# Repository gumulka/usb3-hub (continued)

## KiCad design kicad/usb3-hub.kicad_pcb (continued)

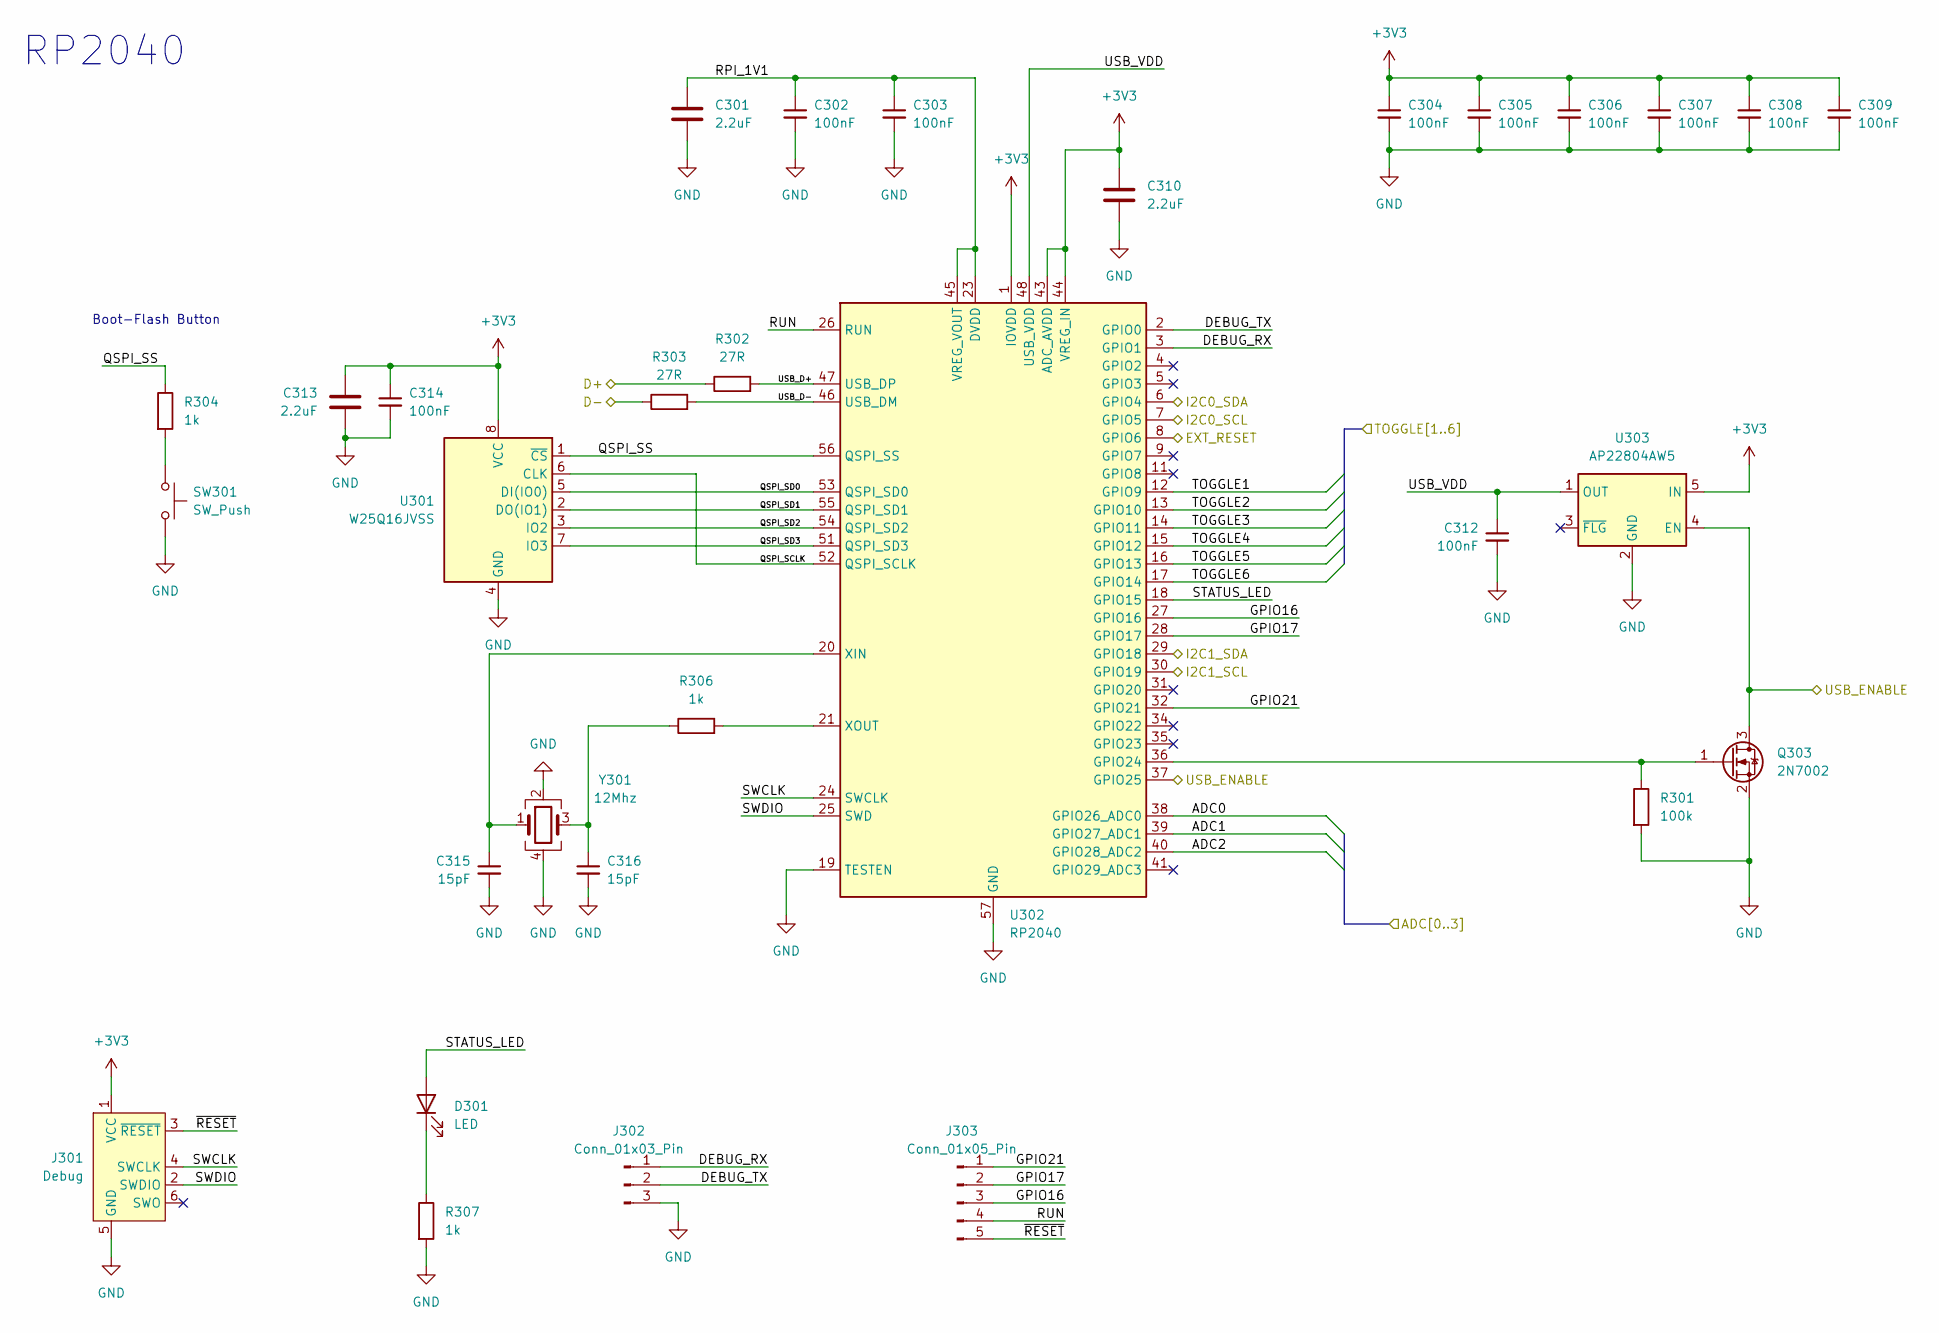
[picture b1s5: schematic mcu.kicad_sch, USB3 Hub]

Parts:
C301, C310, C313: 2.2uF; C_0603_1608Metric
C302, C303, C304, C305, C306, C307, C308, C309, C312, C314: 100nF; C_0402_1005Metric
C315, C316: 15pF; C_0402_1005Metric
D301: LED; LED_0603_1608Metric
J301: Debug; Tag-Connect_TC2030-IDC-NL_2x03_P1.27mm_Vertical
J302: Conn_01x03_Pin; PinHeader_1x03_P2.54mm_Vertical
J303: Conn_01x05_Pin; PinSocket_1x05_P2.54mm_Vertical
Q303: 2N7002; SOT-23
R301: 100k; R_0603_1608Metric
R302, R303: 27R; R_0402_1005Metric
R304, R306, R307: 1k; R_0603_1608Metric
SW301: SW_Push; SW_SPST_TL3342
U301: W25Q16JVSS; SOIC-8_5.23x5.23mm_P1.27mm
U302: RP2040; QFN-56-1EP_7x7mm_P0.4mm_EP3.2x3.2mm
U303: AP22804AW5; SOT-23-5
Y301: 12Mhz; Crystal_SMD_3225-4Pin_3.2x2.5mm; PartNo ABM8-272-T3

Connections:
+3V3: C304.1, C305.1, C306.1, C307.1, C308.1, C309.1, C310.1, C313.1, C314.1, J301.1 (VCC), U301.8 (VCC), U302.1 (IOVDD), U302.10 (IOVDD), U302.22 (IOVDD), U302.33 (IOVDD), U302.42 (IOVDD), U302.43 (ADC_AVDD), U302.44 (VREG_IN), U302.49 (IOVDD), U303.5 (IN); also elsewhere on the board
/ADC0: U302.38 (GPIO26_ADC0); also elsewhere on the board
/ADC1: U302.39 (GPIO27_ADC1); also elsewhere on the board
/ADC2: U302.40 (GPIO28_ADC2); also elsewhere on the board
/Hub/Port7.DP+: R302.1; also elsewhere on the board
/Hub/Port7.DP-: R303.1; also elsewhere on the board
/Hub/Port7.PRT_CTRL: Q303.3 (D), U302.37 (GPIO25), U303.4 (EN); also elsewhere on the board
/Hub/SMB_CLK: U302.7 (GPIO5); also elsewhere on the board
/Hub/SMB_DATA: U302.6 (GPIO4); also elsewhere on the board
/Hub/~RESET: U302.8 (GPIO6); also elsewhere on the board
/Raspberry/DEBUG_RX: J302.1, U302.3 (GPIO1)
/Raspberry/DEBUG_TX: J302.2, U302.2 (GPIO0)
/Raspberry/GPIO16: J303.3, U302.27 (GPIO16)
/Raspberry/GPIO17: J303.2, U302.28 (GPIO17)
/Raspberry/GPIO21: J303.1, U302.32 (GPIO21)
/Raspberry/I2C1_SCL: U302.30 (GPIO19); also elsewhere on the board
/Raspberry/I2C1_SDA: U302.29 (GPIO18); also elsewhere on the board
/Raspberry/QSPI_SCLK: U301.6 (CLK), U302.52 (QSPI_SCLK)
/Raspberry/QSPI_SD0: U301.5 (DI(IO0)), U302.53 (QSPI_SD0)
/Raspberry/QSPI_SD1: U301.2 (DO(IO1)), U302.55 (QSPI_SD1)
/Raspberry/QSPI_SD2: U301.3 (IO2), U302.54 (QSPI_SD2)
/Raspberry/QSPI_SD3: U301.7 (IO3), U302.51 (QSPI_SD3)
/Raspberry/QSPI_SS: R304.1, U301.1 (~CS), U302.56 (QSPI_SS)
/Raspberry/RPI_1V1: C301.1, C302.1, C303.1, U302.23 (DVDD), U302.45 (VREG_VOUT), U302.50 (DVDD)
/Raspberry/RUN: J303.4, U302.26 (RUN)
/Raspberry/STATUS_LED: D301.2 (A), U302.18 (GPIO15)
/Raspberry/SWCLK: J301.4 (SWCLK), U302.24 (SWCLK)
/Raspberry/SWDIO: J301.2 (SWDIO), U302.25 (SWD)
/Raspberry/USB_D+: R302.2, U302.47 (USB_DP)
/Raspberry/USB_D-: R303.2, U302.46 (USB_DM)
/Raspberry/USB_VDD: C312.1, U302.48 (USB_VDD), U303.1 (OUT)
/Raspberry/~RESET: J301.3 (~RESET), J303.5
/TOGGLE1: U302.12 (GPIO9); also elsewhere on the board
/TOGGLE2: U302.13 (GPIO10); also elsewhere on the board
/TOGGLE3: U302.14 (GPIO11); also elsewhere on the board
/TOGGLE4: U302.15 (GPIO12); also elsewhere on the board
/TOGGLE5: U302.16 (GPIO13); also elsewhere on the board
/TOGGLE6: U302.17 (GPIO14); also elsewhere on the board
GND: C301.2, C302.2, C303.2, C304.2, C305.2, C306.2, C307.2, C308.2, C309.2, C310.2, C312.2, C313.2, C314.2, C315.2, C316.2, J301.5 (GND), J302.3, Q303.2 (S), R301.2, R307.2, SW301.2, U301.4 (GND), U302.19 (TESTEN), U302.57 (GND), U303.2 (GND), Y301.2, Y301.4; also elsewhere on the board
unnamed: C316.1, R306.1, Y301.3
unnamed: D301.1 (K), R307.1
unnamed: Q303.1 (G), R301.1, U302.36 (GPIO24)
unnamed: R304.2, SW301.1
unnamed: C315.1, U302.20 (XIN), Y301.1
unnamed: R306.2, U302.21 (XOUT)

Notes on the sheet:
RP2040
Boot-Flash Button

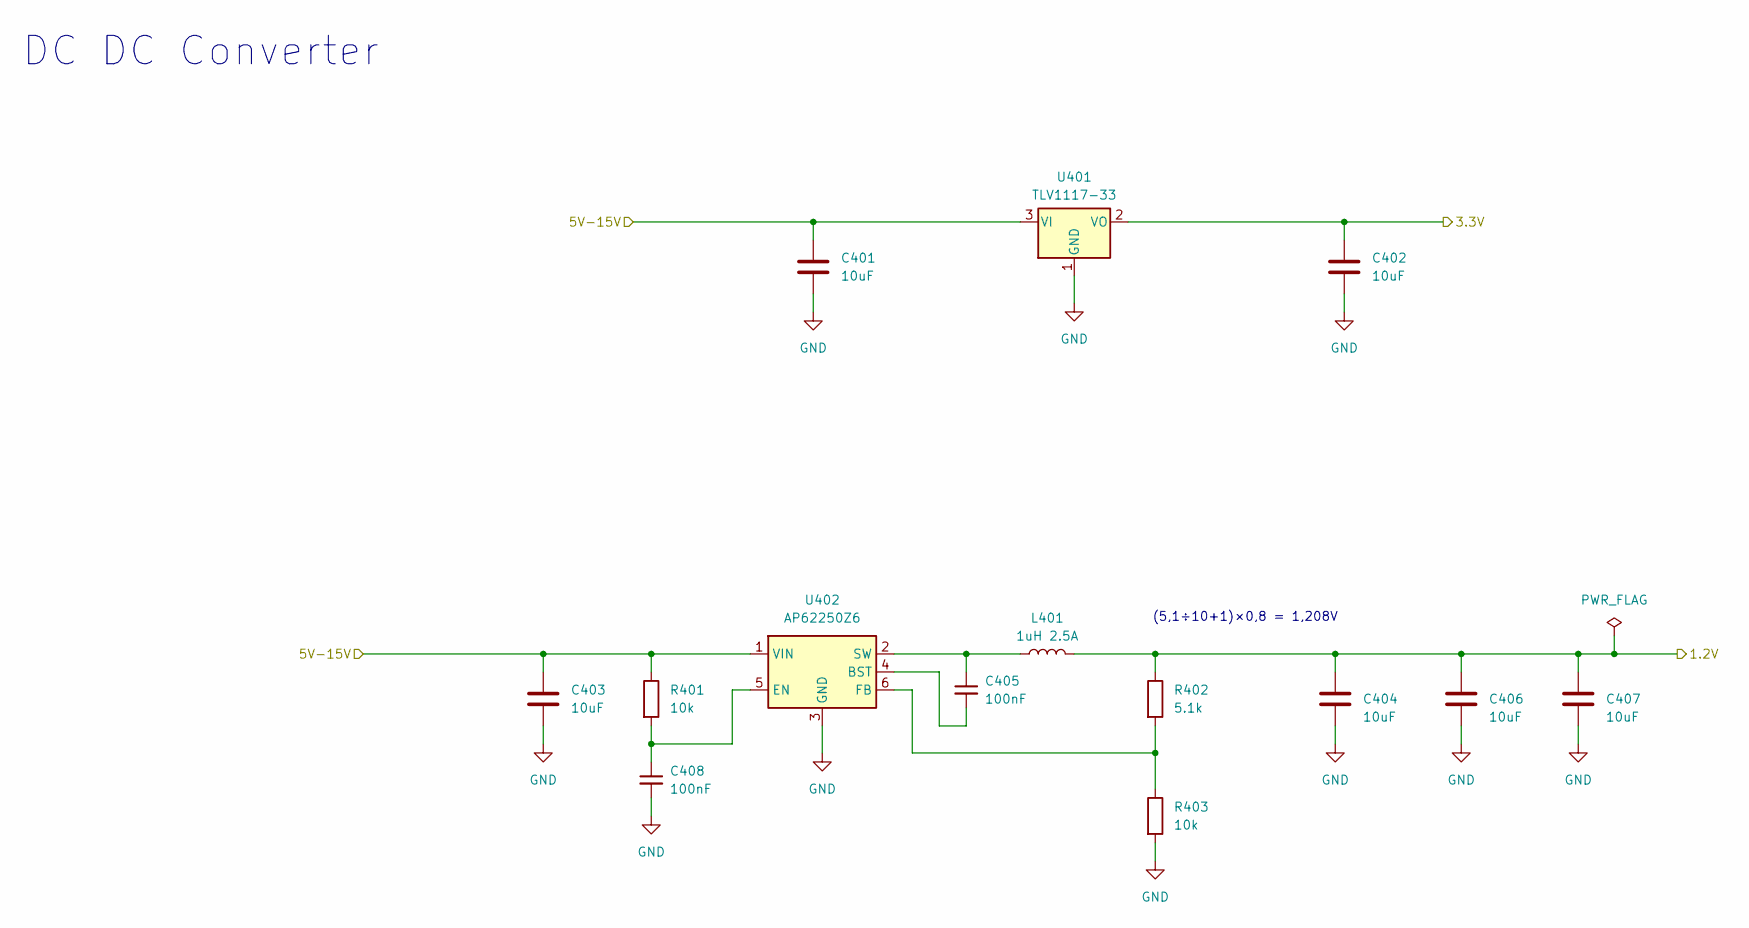
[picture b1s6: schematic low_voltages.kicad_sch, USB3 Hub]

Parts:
C401, C402, C403, C404, C406, C407: 10uF; C_0805_2012Metric
C405, C408: 100nF; C_0402_1005Metric
L401: 1uH 2.5A; L_Bourns-SRN4018
R401, R403: 10k; R_0603_1608Metric
R402: 5.1k; R_0603_1608Metric
U401: TLV1117-33; SOT-223-3_TabPin2
U402: AP62250Z6; SOT-563

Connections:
+1V2: C404.1, C406.1, C407.1, L401.2, R402.1; also elsewhere on the board
+3V3: C402.1, U401.2 (VO); also elsewhere on the board
+5V: C401.1, C403.1, R401.1, U401.3 (VI), U402.1 (VIN); also elsewhere on the board
GND: C401.2, C402.2, C403.2, C404.2, C406.2, C407.2, C408.2, R403.2, U401.1 (GND), U402.3 (GND); also elsewhere on the board
unnamed: C405.2, U402.4 (BST)
unnamed: C408.1, R401.2, U402.5 (EN)
unnamed: R402.2, R403.1, U402.6 (FB)
unnamed: C405.1, L401.1, U402.2 (SW)

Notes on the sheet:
DC DC Converter
(5,1÷10+1)×0,8 = 1,208V

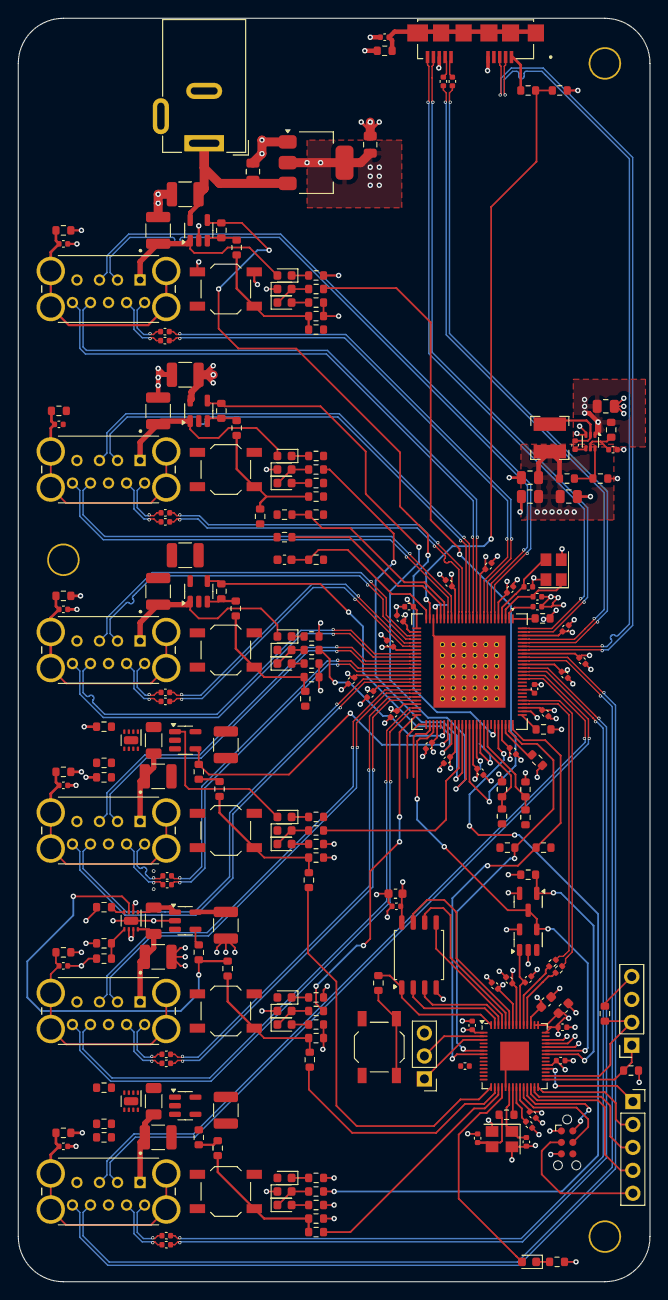
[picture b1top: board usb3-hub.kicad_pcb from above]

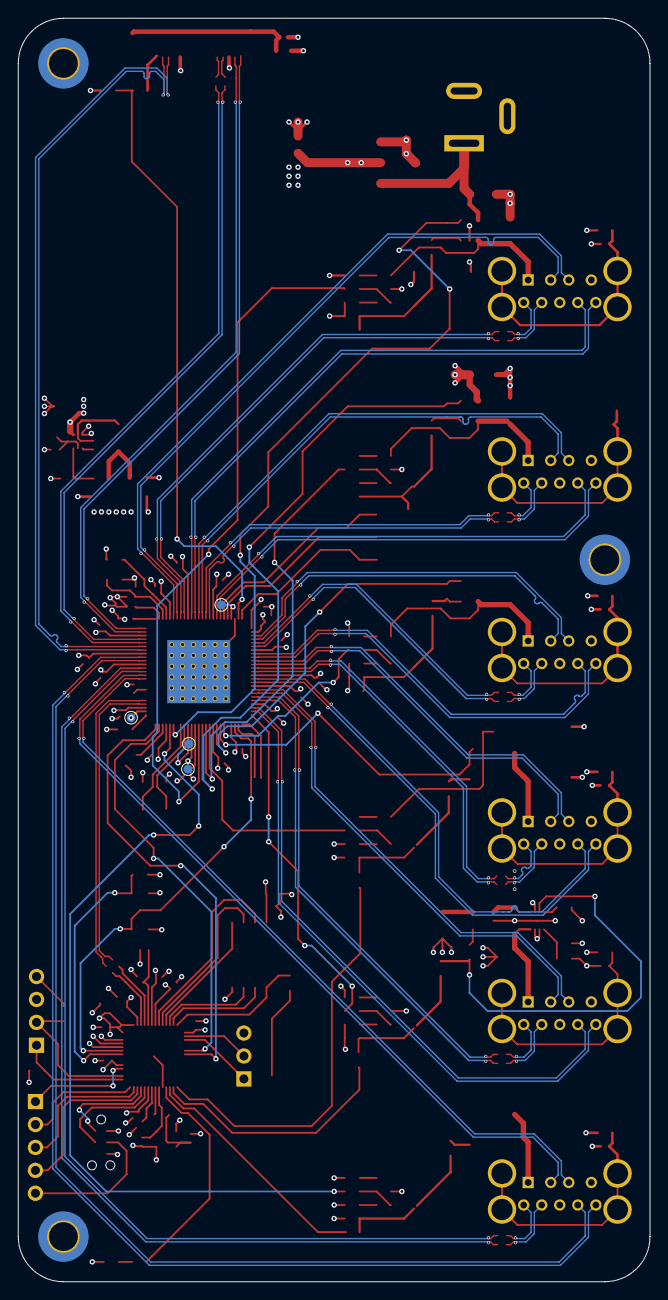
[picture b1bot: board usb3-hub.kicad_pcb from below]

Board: 6 copper layers, 70.0 x 140.0 mm, 229 parts (7 on the bottom side), 186 nets.

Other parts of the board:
D501, D502, D503, D601, D602, D603: LED; LED_0603_1608Metric

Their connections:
/Port4/VBUS_HIGH: D501.2 (A); also elsewhere on the board
/Port5/VBUS_HIGH: D601.2 (A); also elsewhere on the board
GND: D503.1 (K), D603.1 (K); also elsewhere on the board
unnamed 140: D501.1 (K); also elsewhere on the board
unnamed 141: D502.2 (A); also elsewhere on the board
unnamed 142: D502.1 (K), D503.2 (A); also elsewhere on the board
unnamed 143: D601.1 (K); also elsewhere on the board
unnamed 144: D602.2 (A); also elsewhere on the board
unnamed 145: D602.1 (K), D603.2 (A); also elsewhere on the board

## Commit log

2024-09-17 Started with drawing a rough schematic for a hub
    Started drawing a schematic of how a USB3 hub with support for toggling
    the ports via USB-Command and Buttons could look like.
    The Idea is, that the HUB will toggle power output, but can be written
    via SMBUS from the RP2040, which is also connected via a port to the
    USB-Hub, to give feedback about power drawn from the other ports to the
    system for current consumption montoring.
2024-09-17 First rough placement
    Just to get an idea on how it might look like
    Added trace widts for Differential pairs
    Using 6 layers, because it makes power management easier.
    Rather large PCB, but better to big, then to small.
2024-09-17 Added first fanout for usb5807
    Needs a lot more work, but it is a start, that allows me to concentrate
    on the routing of USB signals and have the capacitors relatively close
    to the hub controller.
2024-09-17 Add README with link to the schematics
    Schematics are automatically generated via actions and deployed using
    pages.
2024-09-17 Add check for DRC
    Only checking errors at the moment, as the board is not ready yet
    Moved unconnected Items to severity warning.
2024-09-17 Some more routing
    Not done, but done some more. Nothing is final, just to get a
    better feeling of what could be done.
2024-09-17 Some more routing
    rearranged the LED's
    Exchanged the testpoints with a 1x5 connector.
2024-09-17 Replace 1.2V LDO with switching regulator
    It just feels more reliable.
    Also added 0R resistors between switch and alert signal. My hope is
    that I can tell the switch to diable the port by pulling the
    overcurrent low.
2024-09-18 Add schematics for USB5807 evaluation board
    A lot of information is taken from this schematic for the USB-Hub to
    know how it works and what should or could be there on the pins.
2025-01-05 Some more routing
2025-03-24 Update Pulldown resitor value
    It should not be 1:1, but 1:2 ratio per reference design
